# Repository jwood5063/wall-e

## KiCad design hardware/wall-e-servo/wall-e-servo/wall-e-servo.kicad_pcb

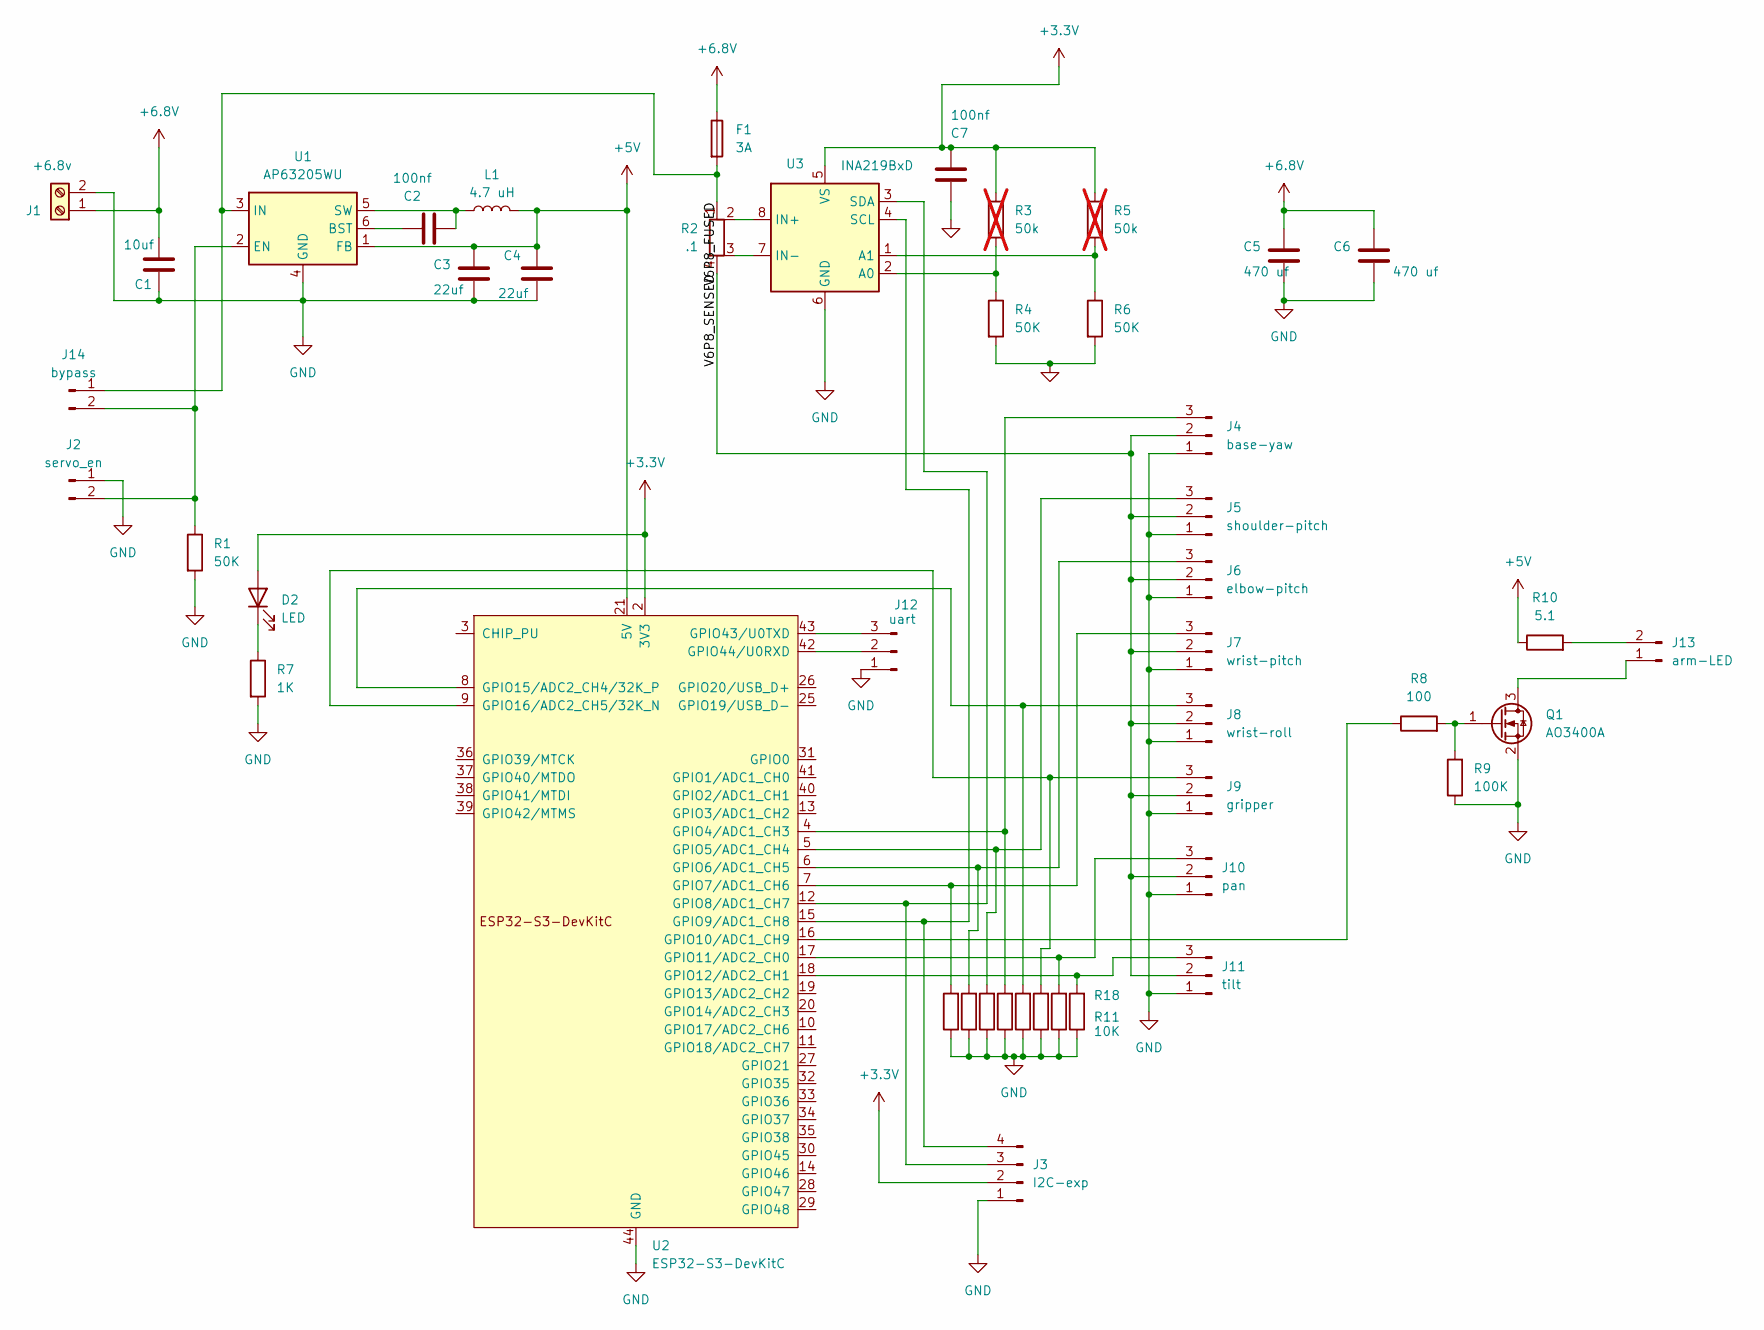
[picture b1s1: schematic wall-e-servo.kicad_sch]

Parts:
C1: 10uf; C_1210_3225Metric_Pad1.33x2.70mm_HandSolder
C2, C7: 100nf; C_0805_2012Metric_Pad1.18x1.45mm_HandSolder
C3, C4: 22uf; C_1210_3225Metric_Pad1.33x2.70mm_HandSolder
C5, C6: 470 uf; CP_Radial_D8.0mm_P3.50mm
D2: LED; LED_D5.0mm
F1: 3A; FuseHolder_Blade_ATO_Littelfuse_FLR_178.6165
J1: +6.8v; TerminalBlock_Phoenix_MKDS-1,5-2-5.08_1x02_P5.08mm_Horizont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
J2: servo_en; JST_PH_B2B-PH-K_1x02_P2.00mm_Vertical
J3: I2C-exp; JST_PH_B4B-PH-K_1x04_P2.00mm_Vertical
J4: base-yaw; PinHeader_1x03_P2.54mm_Vertical
J5: shoulder-pitch; PinHeader_1x03_P2.54mm_Vertical
J6: elbow-pitch; PinHeader_1x03_P2.54mm_Vertical
J7: wrist-pitch; PinHeader_1x03_P2.54mm_Vertical
J8: wrist-roll; PinHeader_1x03_P2.54mm_Vertical
J9: gripper; PinHeader_1x03_P2.54mm_Vertical
J10: pan; PinHeader_1x03_P2.54mm_Vertical
J11: tilt; PinHeader_1x03_P2.54mm_Vertical
J12: uart; JST_PH_B3B-PH-K_1x03_P2.00mm_Vertical
J13: arm-LED; JST_PH_B2B-PH-K_1x02_P2.00mm_Vertical
J14: bypass; PinHeader_1x02_P2.54mm_Vertical
L1: 4.7 uH; L_1806_4516Metric_Pad1.45x1.90mm_HandSolder
Q1: AO3400A; SOT-23
R1, R4, R6: 50K; R_0805_2012Metric_Pad1.20x1.40mm_HandSolder
R2: .1; R_Shunt_Vishay_WSK2512_6332Metric_T1.19mm
R3, R5: 50k; R_0805_2012Metric_Pad1.20x1.40mm_HandSolder; not fitted
R7: 1K; R_Axial_DIN0207_L6.3mm_D2.5mm_P10.16mm_Horizontal
R8: 100; R_0805_2012Metric_Pad1.20x1.40mm_HandSolder
R9: 100K; R_0805_2012Metric_Pad1.20x1.40mm_HandSolder
R10: 5.1; R_2512_6332Metric_Pad1.40x3.35mm_HandSolder
R11, R12, R13, R14, R15, R16, R17, R18: 10K; R_0805_2012Metric_Pad1.20x1.40mm_HandSolder
U1: AP63205WU; TSOT-23-6
U2: ESP32-S3-DevKitC
U3: INA219BxD; SOIC-8_3.9x4.9mm_P1.27mm

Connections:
+3.3V: C7.2, D2.2 (A), J3.2, R3.1, R5.1, U2.1 (3V3), U2.2 (3V3), U3.5 (VS)
+5V: C3.1, C4.1, L1.2, R10.1, U1.1 (FB), U2.21 (5V)
+6.8V: C1.1, C5.1, C6.1, F1.1, J1.1
/V6P8_FUSED: F1.2, J14.1, R2.1, U1.3 (IN)
/V6P8_SENSED: J4.2, J5.2, J6.2, J7.2, J8.2, J9.2, J10.2, J11.2, R2.4
GND: C1.2, C3.2, C4.2, C5.2, C6.2, C7.1, J1.2, J2.1, J3.1, J4.1, J5.1, J6.1, J7.1, J8.1, J9.1, J10.1, J11.1, J12.1, Q1.2 (S), R1.2, R4.2, R6.2, R7.2, R9.1, R11.1, R12.1, R13.1, R14.1, R15.1, R16.1, R17.1, R18.1, U1.4 (GND), U2.22 (GND), U2.23 (GND), U2.24 (GND), U2.44 (GND), U3.6 (GND)
unnamed: D2.1 (K), R7.1
unnamed: J3.3, U2.12 (GPIO8/ADC1_CH7), U3.3 (SDA)
unnamed: J3.4, U2.15 (GPIO9/ADC1_CH8), U3.4 (SCL)
unnamed: J4.3, R15.2, U2.4 (GPIO4/ADC1_CH3)
unnamed: J5.3, R16.2, U2.5 (GPIO5/ADC1_CH4)
unnamed: J6.3, R17.2, U2.6 (GPIO6/ADC1_CH5)
unnamed: J7.3, R18.2, U2.7 (GPIO7/ADC1_CH6)
unnamed: J8.3, R14.2, U2.8 (GPIO15/ADC2_CH4/32K_P)
unnamed: J9.3, R13.2, U2.9 (GPIO16/ADC2_CH5/32K_N)
unnamed: J10.3, R12.2, U2.17 (GPIO11/ADC2_CH0)
unnamed: J11.3, R11.2, U2.18 (GPIO12/ADC2_CH1)
unnamed: J12.2, U2.42 (GPIO44/U0RXD)
unnamed: J12.3, U2.43 (GPIO43/U0TXD)
unnamed: J13.1, Q1.3 (D)
unnamed: J13.2, R10.2
unnamed: J2.2, J14.2, R1.1, U1.2 (EN)
unnamed: Q1.1 (G), R8.2, R9.2
unnamed: C2.1, U1.6 (BST)
unnamed: C2.2, L1.1, U1.5 (SW)
unnamed: R8.1, U2.16 (GPIO10/ADC1_CH9)
unnamed: R3.2, R4.1, U3.2 (A0)
unnamed: R5.2, R6.1, U3.1 (A1)
unnamed: R2.2, U3.8 (IN+)
unnamed: R2.3, U3.7 (IN-)

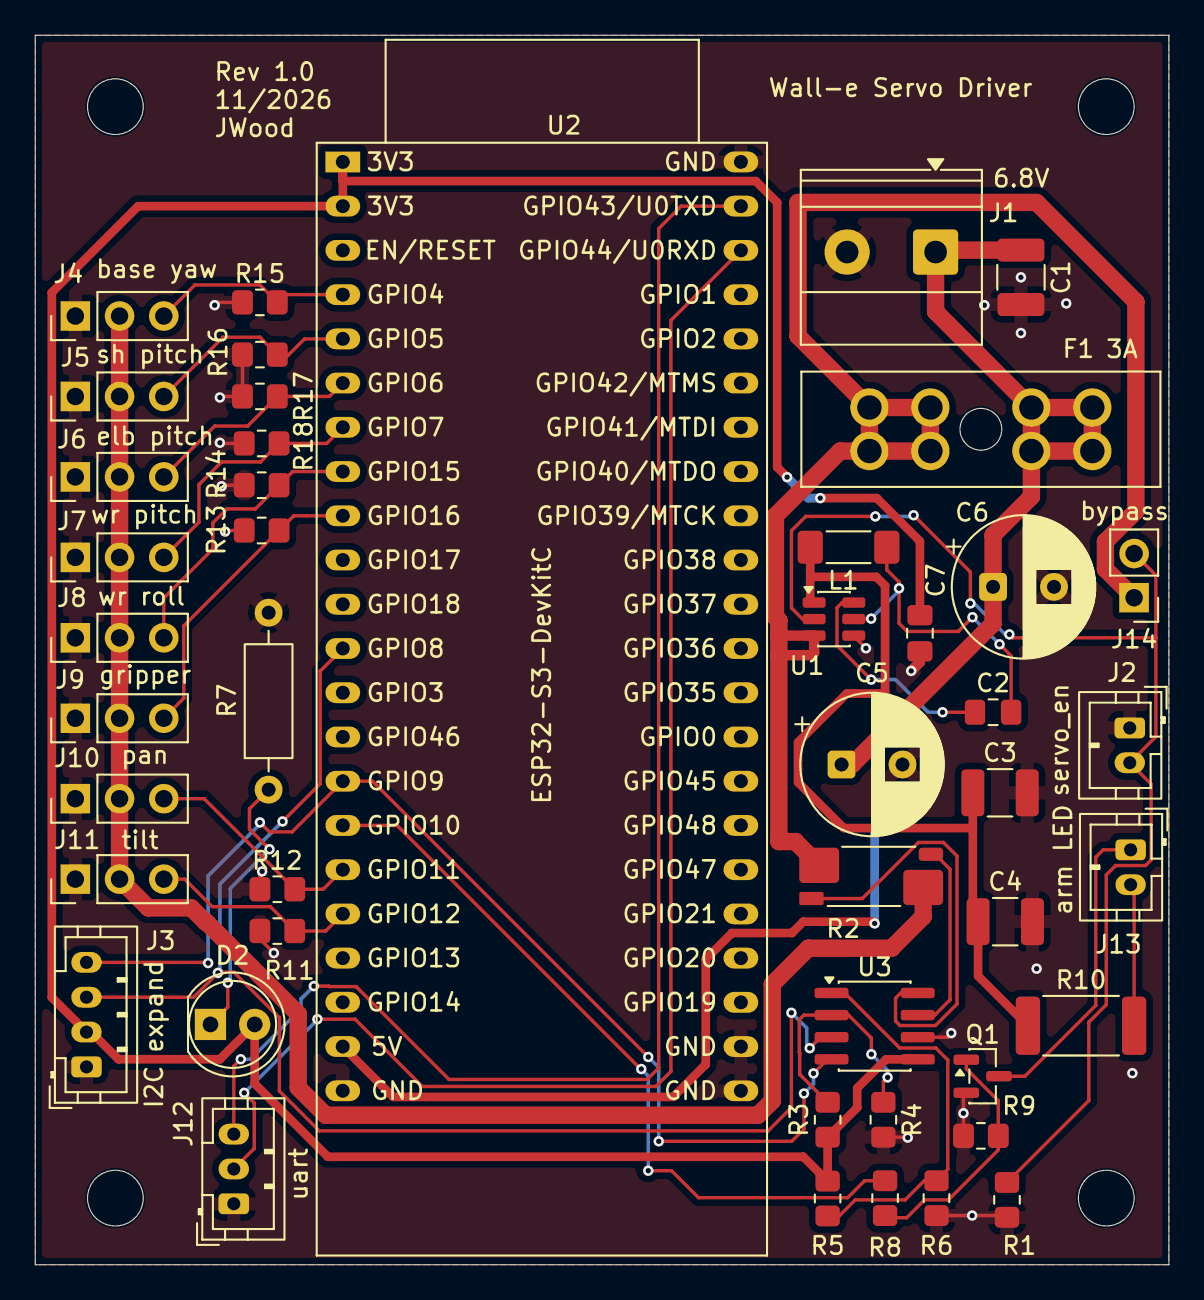
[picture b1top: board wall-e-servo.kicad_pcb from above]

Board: 2 copper layers, 65.1 x 70.6 mm, 46 parts (0 on the bottom side), 30 nets.

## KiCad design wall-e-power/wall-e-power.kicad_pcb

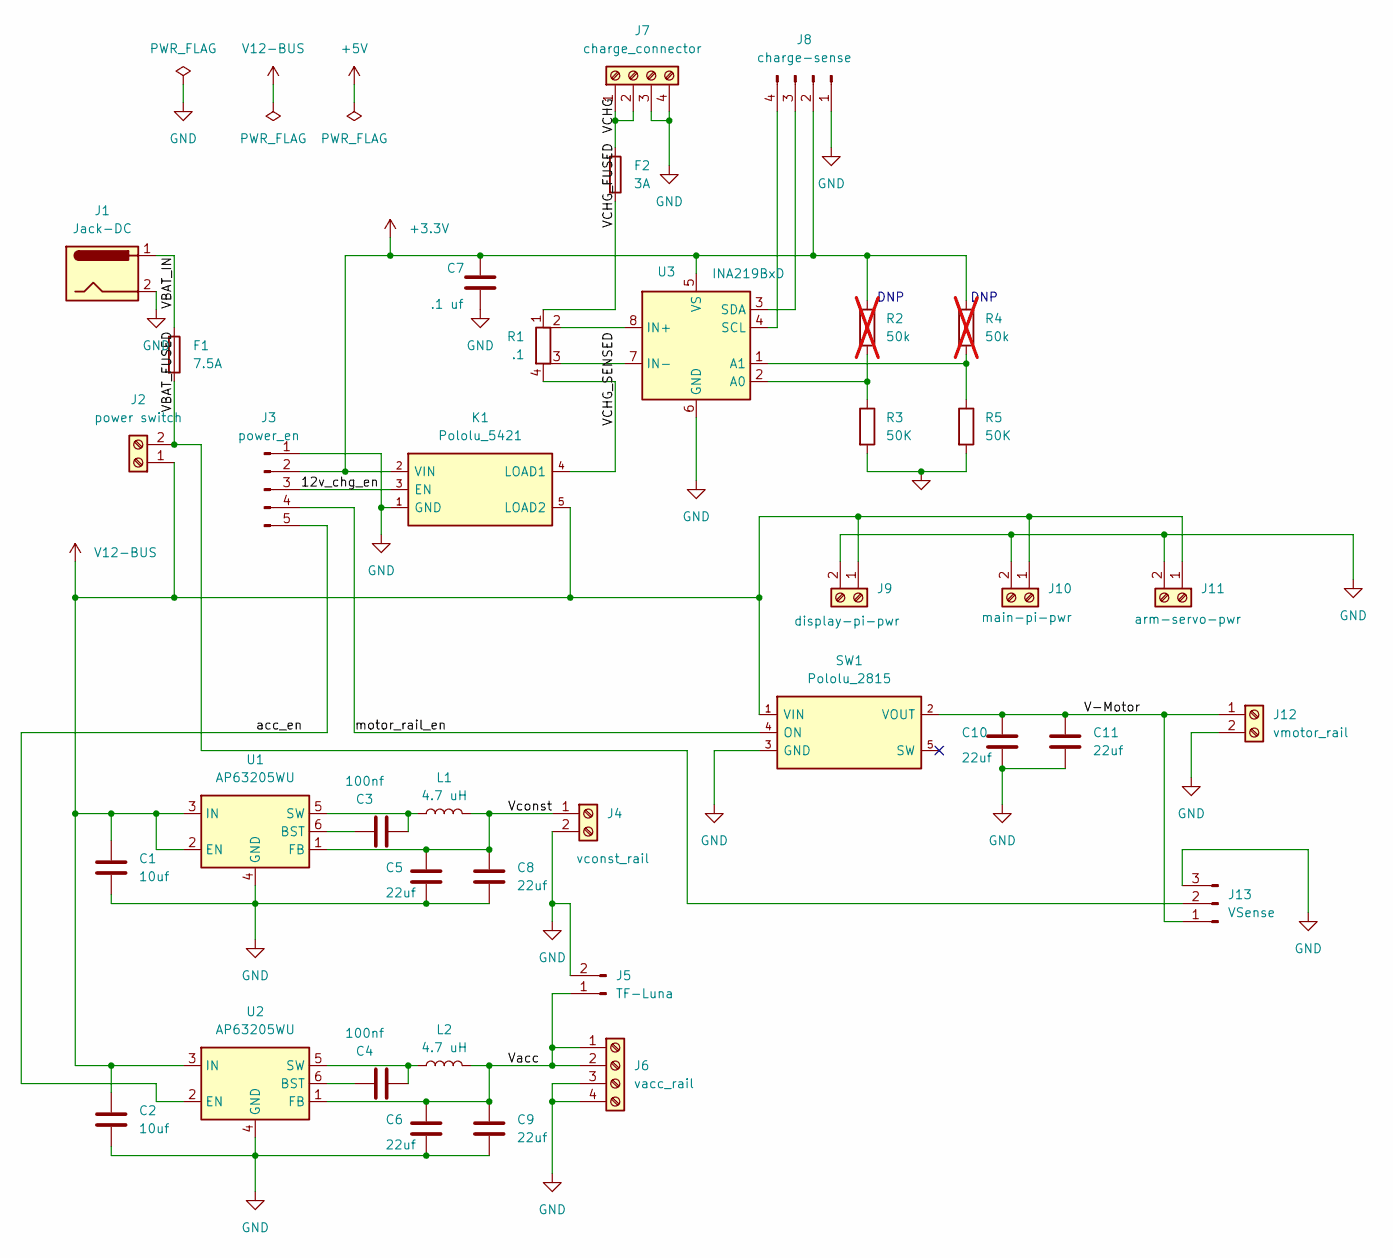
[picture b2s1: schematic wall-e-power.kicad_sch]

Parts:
C1, C2: 10uf; C_1210_3225Metric_Pad1.33x2.70mm_HandSolder
C3, C4: 100nf; C_0805_2012Metric_Pad1.18x1.45mm_HandSolder
C5, C6, C8, C9, C10, C11: 22uf; C_1210_3225Metric_Pad1.33x2.70mm_HandSolder
C7: .1 uf; C_0805_2012Metric_Pad1.18x1.45mm_HandSolder
F1: 7.5A; FuseHolder_Blade_ATO_Littelfuse_FLR_178.6165
F2: 3A; FuseHolder_Blade_ATO_Littelfuse_FLR_178.6165
J1: Jack-DC; BarrelJack_Tensility_54-00131
J2: power switch; TerminalBlock_Phoenix_MKDS-1,5-2-5.08_1x02_P5.08mm_Horizont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
J3: power_en; JST_PH_B5B-PH-K_1x05_P2.00mm_Vertical
J4: vconst_rail; TerminalBlock_Phoenix_MKDS-1,5-2-5.08_1x02_P5.08mm_Horizont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
J5: TF-Luna; JST_PH_B2B-PH-K_1x02_P2.00mm_Vertical
J6: vacc_rail; TerminalBlock_RND_205-00003_1x04_P5.00mm_Horizontal
J7: charge_connector; TerminalBlock_RND_205-00003_1x04_P5.00mm_Horizontal
J8: charge-sense; JST_PH_B4B-PH-K_1x04_P2.00mm_Vertical
J9: display-pi-pwr; TerminalBlock_Phoenix_MKDS-1,5-2-5.08_1x02_P5.08mm_Horizont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
J10: main-pi-pwr; TerminalBlock_Phoenix_MKDS-1,5-2-5.08_1x02_P5.08mm_Horizont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
J11: arm-servo-pwr; TerminalBlock_Phoenix_MKDS-1,5-2-5.08_1x02_P5.08mm_Horizont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
J12: vmotor_rail; TerminalBlock_Phoenix_MKDS-1,5-2-5.08_1x02_P5.08mm_Horizont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
J13: VSense; JST_PH_B3B-PH-K_1x03_P2.00mm_Vertical
K1: Pololu_5421; Pololu_5421_THT
L1, L2: 4.7 uH; L_1806_4516Metric_Pad1.45x1.90mm_HandSolder
R1: .1; R_Shunt_Vishay_WSK2512_6332Metric_T1.19mm
R2, R4: 50k; R_0805_2012Metric_Pad1.20x1.40mm_HandSolder; not fitted
R3, R5: 50K; R_0805_2012Metric_Pad1.20x1.40mm_HandSolder
SW1: Pololu_2815; Pololu_2815_THT
U1, U2: AP63205WU; TSOT-23-6
U3: INA219BxD; SOIC-8_3.9x4.9mm_P1.27mm

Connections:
+3.3V: C7.1, J3.2, J8.2, K1.2 (VIN), R2.1, R4.1, U3.5 (VS)
/12v_chg_en: J3.3, K1.3 (EN)
/V-Motor: C10.1, C11.1, J12.1, J13.1, SW1.2 (VOUT)
/VBAT_FUSED: F1.2, J2.2, J13.2
/VBAT_IN: F1.1, J1.1
/VCHG: F2.1, J7.1, J7.2
/VCHG_FUSED: F2.2, R1.1
/VCHG_SENSED: K1.4 (LOAD1), R1.4
/Vacc: C6.1, C9.1, J5.1, J6.1, J6.2, L2.2, U2.1 (FB)
/Vconst: C5.1, C8.1, J4.1, L1.2, U1.1 (FB)
/acc_en: J3.5, U2.2 (EN)
/motor_rail_en: J3.4, SW1.4 (ON)
GND: C1.2, C2.2, C5.2, C6.2, C7.2, C8.2, C9.2, C10.2, C11.2, J1.2, J3.1, J4.2, J5.2, J6.3, J6.4, J7.3, J7.4, J8.1, J9.2, J10.2, J11.2, J12.2, J13.3, K1.1 (GND), R3.2, R5.2, SW1.3 (GND), U1.4 (GND), U2.4 (GND), U3.6 (GND)
unnamed: J8.3, U3.3 (SDA)
unnamed: J8.4, U3.4 (SCL)
unnamed: C3.1, U1.6 (BST)
unnamed: C3.2, L1.1, U1.5 (SW)
unnamed: C4.1, U2.6 (BST)
unnamed: C4.2, L2.1, U2.5 (SW)
unnamed: R2.2, R3.1, U3.2 (A0)
unnamed: R4.2, R5.1, U3.1 (A1)
unnamed: R1.2, U3.8 (IN+)
unnamed: R1.3, U3.7 (IN-)
V12-BUS: C1.1, C2.1, J2.1, J9.1, J10.1, J11.1, K1.5 (LOAD2), SW1.1 (VIN), U1.2 (EN), U1.3 (IN), U2.3 (IN)

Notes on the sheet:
DNP
DNP

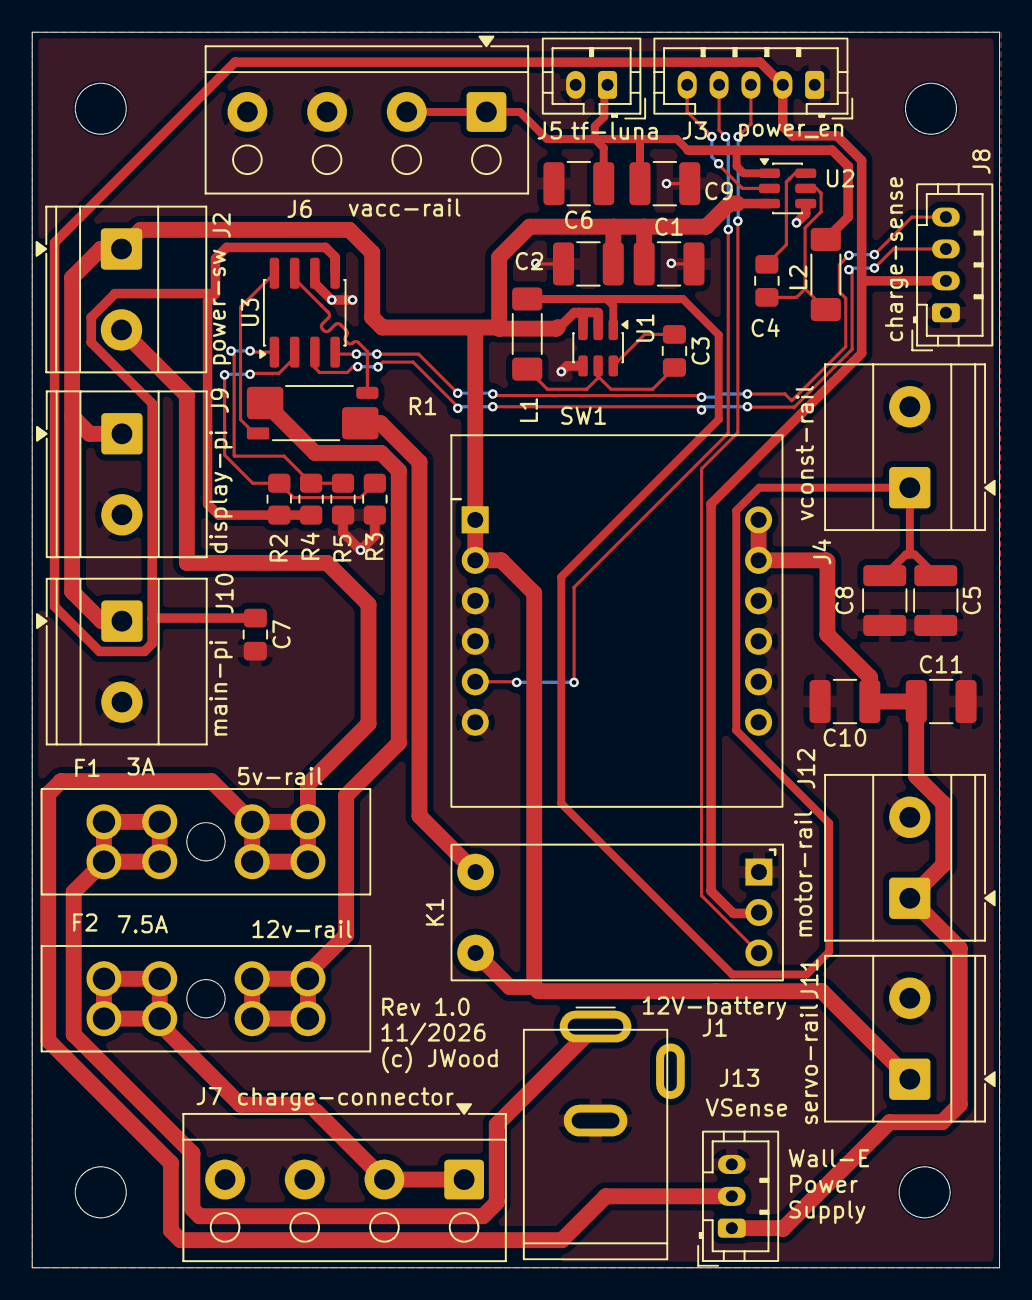
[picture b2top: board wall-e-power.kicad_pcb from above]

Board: 2 copper layers, 60.7 x 77.5 mm, 38 parts (0 on the bottom side), 24 nets.

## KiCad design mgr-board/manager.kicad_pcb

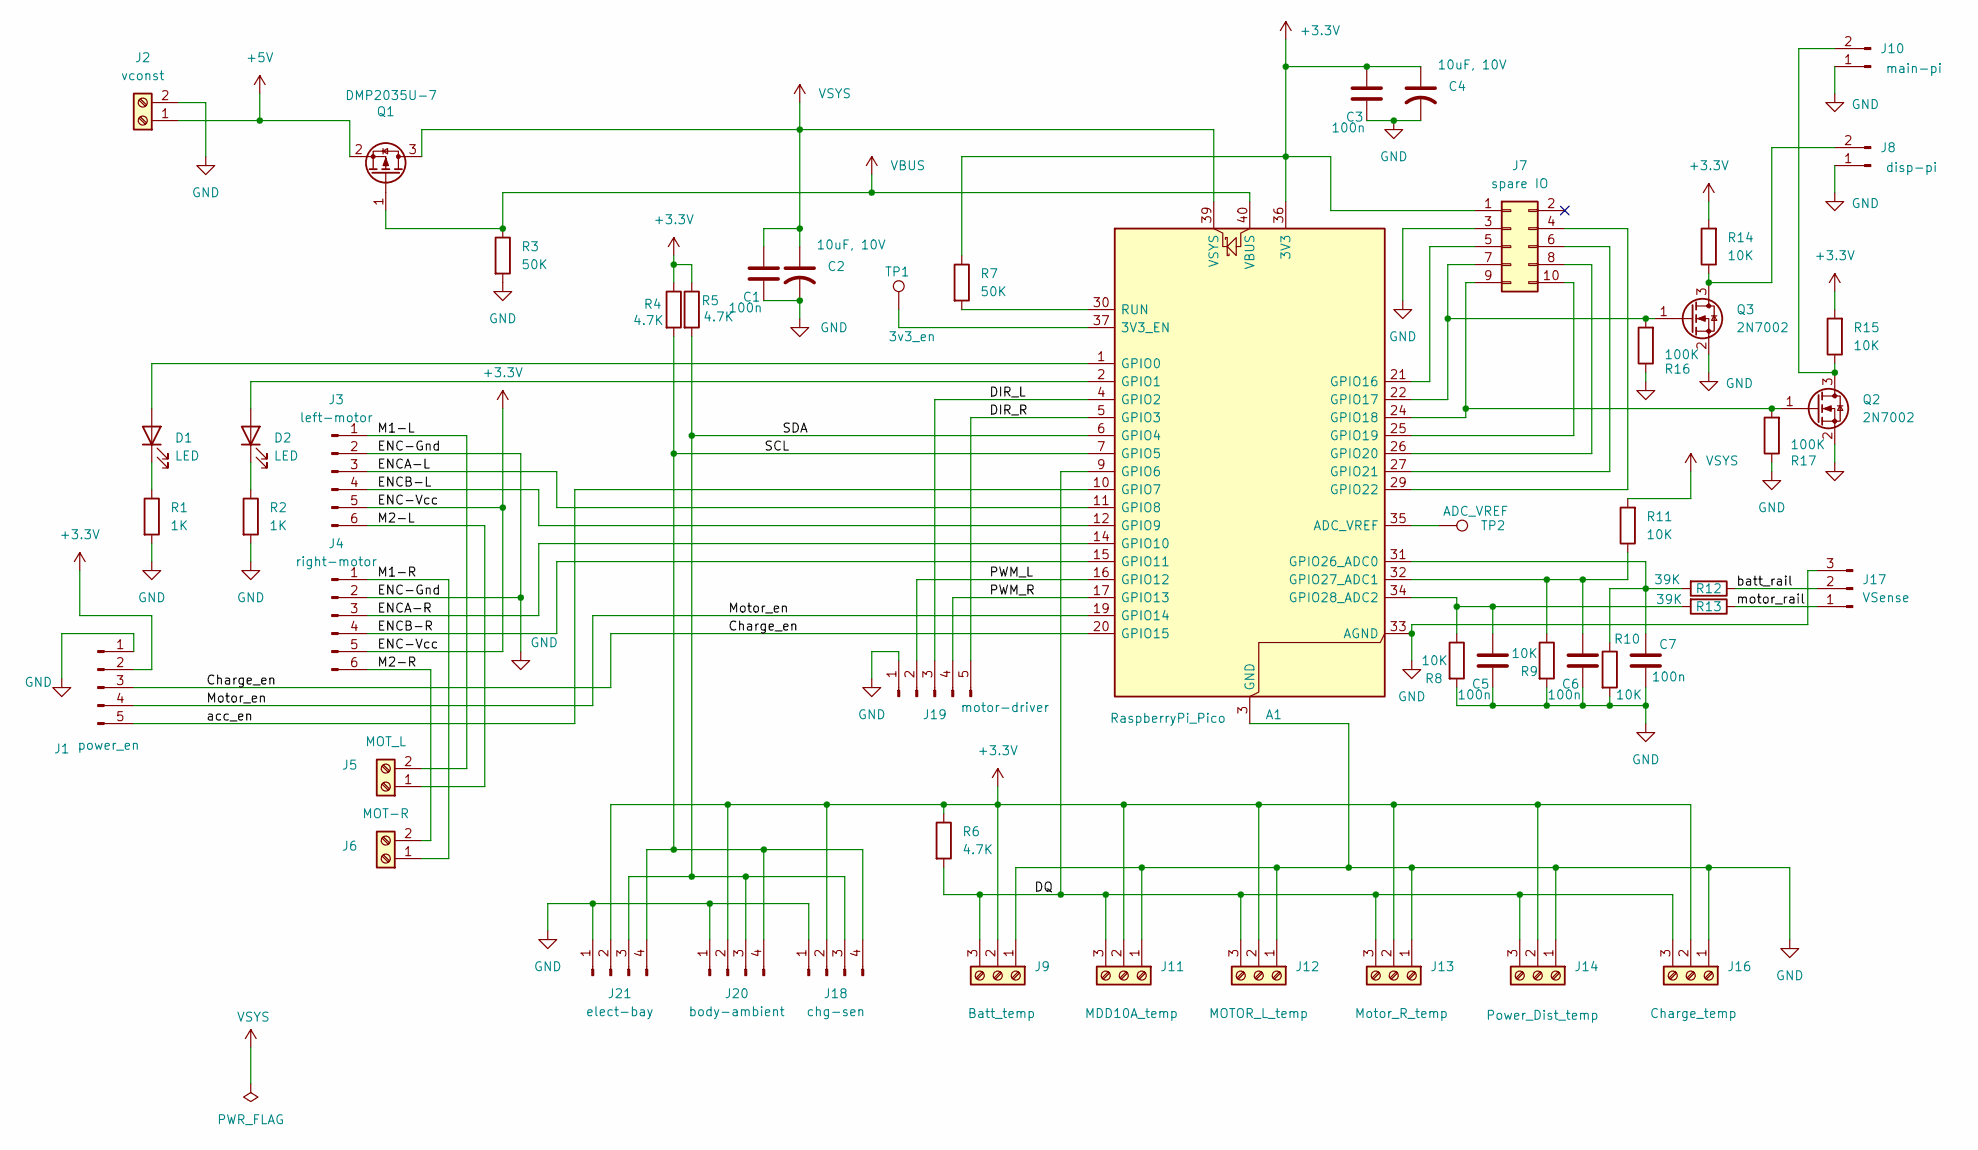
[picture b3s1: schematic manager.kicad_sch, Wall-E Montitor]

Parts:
A1: RaspberryPi_Pico; RaspberryPi_Pico_Common_THT
C1, C3, C5, C6, C7: 100n; C_Disc_D5.0mm_W2.5mm_P2.50mm
C2, C4: 10uF, 10V; C_Radial_D4.0mm_H5.0mm_P1.50mm
D1, D2: LED; LED_D5.0mm
J1: power_en; JST_PH_B5B-PH-K_1x05_P2.00mm_Vertical
J2: vconst; TerminalBlock_RND_205-00012_1x02_P5.00mm_Horizontal
J3: left-motor; JST_PH_B6B-PH-K_1x06_P2.00mm_Vertical
J4: right-motor; JST_PH_B6B-PH-K_1x06_P2.00mm_Vertical
J5: MOT_L; TerminalBlock_RND_205-00012_1x02_P5.00mm_Horizontal
J6: MOT-R; TerminalBlock_RND_205-00012_1x02_P5.00mm_Horizontal
J7: spare IO; PinHeader_2x05_P2.54mm_Vertical
J8: disp-pi; JST_PH_B2B-PH-K_1x02_P2.00mm_Vertical
J9: Batt_temp; TerminalBlock_RND_205-00002_1x03_P5.00mm_Horizontal
J10: main-pi; JST_PH_B2B-PH-K_1x02_P2.00mm_Vertical
J11: MDD10A_temp; TerminalBlock_RND_205-00002_1x03_P5.00mm_Horizontal
J12: MOTOR_L_temp; TerminalBlock_RND_205-00002_1x03_P5.00mm_Horizontal
J13: Motor_R_temp; TerminalBlock_RND_205-00002_1x03_P5.00mm_Horizontal
J14: Power_Dist_temp; TerminalBlock_RND_205-00002_1x03_P5.00mm_Horizontal
J16: Charge_temp; TerminalBlock_RND_205-00002_1x03_P5.00mm_Horizontal
J17: VSense; JST_PH_B3B-PH-K_1x03_P2.00mm_Vertical
J18: chg-sen; JST_PH_B4B-PH-K_1x04_P2.00mm_Vertical
J19: motor-driver; JST_PH_B5B-PH-K_1x05_P2.00mm_Vertical
J20: body-ambient; JST_PH_B4B-PH-K_1x04_P2.00mm_Vertical
J21: elect-bay; JST_PH_B4B-PH-K_1x04_P2.00mm_Vertical
Q1: DMP2035U-7; SOT-23
Q2, Q3: 2N7002; SOT-23
R1, R2: 1K; R_Axial_DIN0207_L6.3mm_D2.5mm_P10.16mm_Horizontal
R3, R7: 50K; R_Axial_DIN0207_L6.3mm_D2.5mm_P10.16mm_Horizontal
R4, R5, R6: 4.7K; R_Axial_DIN0207_L6.3mm_D2.5mm_P10.16mm_Horizontal
R8, R9, R10, R11, R14, R15: 10K; R_Axial_DIN0207_L6.3mm_D2.5mm_P10.16mm_Horizontal
R12, R13: 39K; R_Axial_DIN0207_L6.3mm_D2.5mm_P10.16mm_Horizontal
R16, R17: 100K; R_Axial_DIN0207_L6.3mm_D2.5mm_P10.16mm_Horizontal
TP1: 3v3_en; PinHeader_1x01_P2.54mm_Vertical
TP2: ADC_VREF; PinHeader_1x01_P2.54mm_Vertical

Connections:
+3.3V: A1.36 (3V3), C3.1, C4.1, J1.2, J3.5, J4.5, J7.1, J9.2, J11.2, J12.2, J13.2, J14.2, J16.2, J18.2, J20.2, J21.2, R4.1, R5.1, R6.1, R7.1, R14.2, R15.2
+5V: J2.1, Q1.2 (S)
/Charge_en: A1.20 (GPIO15), J1.3
/DIR_L: A1.4 (GPIO2), J19.3
/DIR_R: A1.5 (GPIO3), J19.5
/DQ: A1.9 (GPIO6), J9.3, J11.3, J12.3, J13.3, J14.3, J16.3, R6.2
/ENCA-L: A1.11 (GPIO8), J3.3
/ENCA-R: A1.14 (GPIO10), J4.3
/ENCB-L: A1.12 (GPIO9), J3.4
/ENCB-R: A1.15 (GPIO11), J4.4
/M1-L: J3.1, J5.2
/M1-R: J4.1, J6.1
/M2-L: J3.6, J5.1
/M2-R: J4.6, J6.2
/Motor_en: A1.19 (GPIO14), J1.4
/PWM_L: A1.16 (GPIO12), J19.2
/PWM_R: A1.17 (GPIO13), J19.4
/SCL: A1.7 (GPIO5), J18.4, J20.4, J21.4, R4.2
/SDA: A1.6 (GPIO4), J18.3, J20.3, J21.3, R5.2
/acc_en: A1.10 (GPIO7), J1.5
/batt_rail: J17.2, R12.1
/motor_rail: J17.1, R13.1
GND: A1.3 (GND), A1.8 (GND), A1.13 (GND), A1.18 (GND), A1.23 (GND), A1.28 (GND), A1.33 (AGND), A1.38 (GND), C1.2, C2.2, C3.2, C4.2, C5.2, C6.2, C7.2, J1.1, J2.2, J3.2, J4.2, J7.3, J8.1, J9.1, J10.1, J11.1, J12.1, J13.1, J14.1, J16.1, J17.3, J18.1, J19.1, J20.1, J21.1, Q2.2 (S), Q3.2 (S), R1.2, R2.2, R3.2, R8.2, R9.2, R10.2, R16.1, R17.1; also elsewhere on the board
unnamed: A1.37 (3V3_EN), TP1.1 (1_1)
unnamed: A1.35 (ADC_VREF), TP2.1 (1_1)
unnamed: A1.1 (GPIO0), D1.2 (A)
unnamed: A1.2 (GPIO1), D2.2 (A)
unnamed: A1.21 (GPIO16), J7.5
unnamed: A1.22 (GPIO17), J7.7, Q3.1 (G), R16.2
unnamed: A1.24 (GPIO18), J7.9, Q2.1 (G), R17.2
unnamed: A1.25 (GPIO19), J7.10
unnamed: A1.26 (GPIO20), J7.8
unnamed: A1.27 (GPIO21), J7.6
unnamed 33: A1.29 (GPIO22), J7.4; also elsewhere on the board
unnamed: A1.31 (GPIO26_ADC0), C7.1, R10.1, R12.2
unnamed: A1.32 (GPIO27_ADC1), C6.1, R9.1, R11.1
unnamed: A1.34 (GPIO28_ADC2), C5.1, R8.1, R13.2
unnamed: A1.30 (RUN), R7.2
unnamed: D1.1 (K), R1.1
unnamed: D2.1 (K), R2.1
unnamed: J8.2, Q3.3 (D), R14.1
unnamed: J10.2, Q2.3 (D), R15.1
VBUS: A1.40 (VBUS), Q1.1 (G), R3.1
VSYS: A1.39 (VSYS), C1.1, C2.1, Q1.3 (D), R11.2

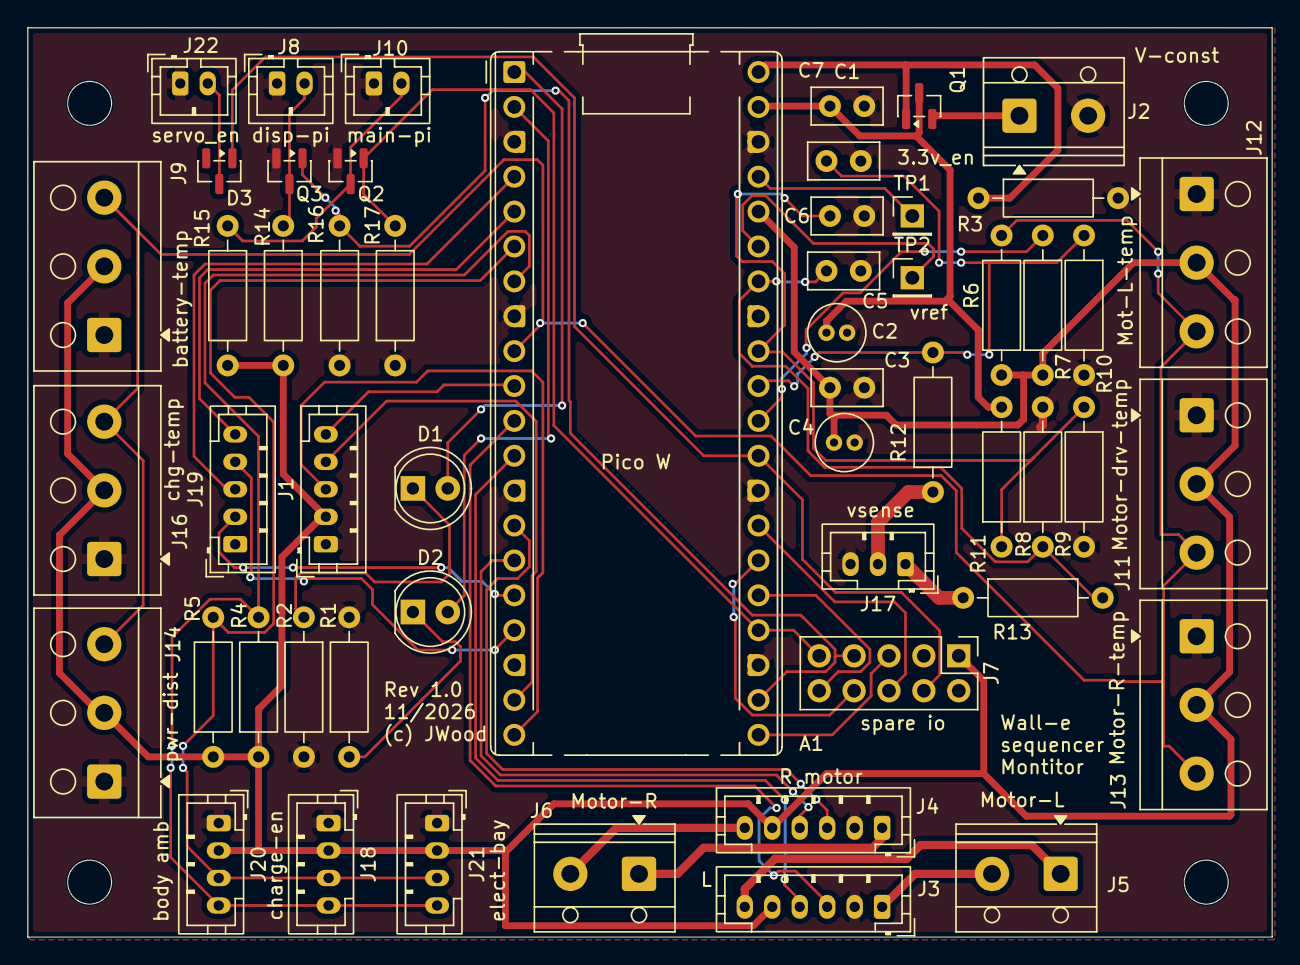
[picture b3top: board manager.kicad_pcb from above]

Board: 2 copper layers, 90.6 x 66.2 mm, 54 parts (0 on the bottom side), 45 nets.

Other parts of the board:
D3: BAT54C; SOT-23
J22: servo_en; JST_PH_B2B-PH-K_1x02_P2.00mm_Vertical

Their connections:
GND: J22.1; also elsewhere on the board
unnamed 33: D3.1; also elsewhere on the board
unnamed: D3.3, J22.2

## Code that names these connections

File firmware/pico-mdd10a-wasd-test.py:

# pico-mdd10a-wasd-test.py
# MicroPython bench test for the Cytron MDD10A, driven by the Pico over USB serial.
#
# Keys (in the serial terminal / REPL):
#   w = both motors forward      s = both motors reverse
#   a = pivot left  (L rev, R fwd)   d = pivot right (L fwd, R rev)
#   x or SPACE = stop
#   + / - = speed up / slow down (10% steps, applies to the next command)
#   h = help
#
# Wiring (Pico carrier J2 assignment, verified 2026-11-05):
#   PWM_L = GP12, DIR_L = GP2, PWM_R = GP13, DIR_R = GP3, common GND.
# Sign-magnitude drive per the MDD10A truth table: DIR low = forward
# (output A high), DIR high = reverse; speed = PWM duty. PWM at 20 kHz,
# the MDD10A's rated maximum. Duty ramps so the motors (or the meter, in
# the unloaded test) never see a step change.
#
# Note: with a straight cable to the MDD10A today, these "left" signals land
# on the driver's channel 2 and "right" on channel 1 (the board's input order
# is PWM2/DIR2 before PWM1/DIR1). Irrelevant for this test; the carrier J2
# re-pin to match is a recorded relayout to-do (2026-11-16).

import sys
import select
import time
from machine import Pin, PWM

PWM_FREQ = 20000
RAMP_STEP = 0.05          # duty change per tick (~0.4 s from stop to full)
TICK_MS = 20

pwm_l = PWM(Pin(12))
pwm_l.freq(PWM_FREQ)
dir_l = Pin(2, Pin.OUT, value=0)
pwm_r = PWM(Pin(13))
pwm_r.freq(PWM_FREQ)
dir_r = Pin(3, Pin.OUT, value=0)


def drive(pwm, dir_pin, value):
    """value: -1.0..1.0, sign = direction, magnitude = duty."""
    dir_pin.value(0 if value >= 0 else 1)
    pwm.duty_u16(int(abs(value) * 65535))


def stop_all():
    drive(pwm_l, dir_l, 0)
    drive(pwm_r, dir_r, 0)


speed = 0.4               # commanded duty for w/a/s/d, adjustable with +/-
cur_l = cur_r = 0.0       # ramped (actual) outputs
tgt_l = tgt_r = 0.0       # commanded targets

COMMANDS = {
    "w": lambda s: (s, s),
    "s": lambda s: (-s, -s),
    "a": lambda s: (-s, s),   # pivot left: left track back, right track forward
    "d": lambda s: (s, -s),   # pivot right
}

HELP = __doc__

print("MDD10A WASD test — PWM_L GP12, DIR_L GP2, PWM_R GP13, DIR_R GP3")
print("w/a/s/d drive, x or space stops, +/- speed, h help. Speed starts at 40%.")

poller = select.poll()
poller.register(sys.stdin, select.POLLIN)
stdin = sys.stdin.buffer if hasattr(sys.stdin, "buffer") else sys.stdin

try:
    while True:
        if poller.poll(0):
            ch = stdin.read(1).decode().lower()
            if ch in COMMANDS:
                tgt_l, tgt_r = COMMANDS[ch](speed)
                print("cmd", ch, "-> L {:+.0f}%  R {:+.0f}%".format(tgt_l * 100, tgt_r * 100))
            elif ch in ("x", " "):
                tgt_l = tgt_r = 0.0
                print("stop")
            elif ch in ("+", "="):
                speed = min(1.0, speed + 0.1)
                print("speed {:.0f}% (applies to next w/a/s/d)".format(speed * 100))
            elif ch == "-":
                speed = max(0.1, speed - 0.1)
                print("speed {:.0f}% (applies to next w/a/s/d)".format(speed * 100))
            elif ch == "h":
                print(HELP)
            # anything else (incl. \r, \n) is ignored

        # Ramp actual outputs toward targets, then apply.
        for name in ("l", "r"):
            cur = cur_l if name == "l" else cur_r
            tgt = tgt_l if name == "l" else tgt_r
            if cur < tgt:
                cur = min(tgt, cur + RAMP_STEP)
            elif cur > tgt:
                cur = max(tgt, cur - RAMP_STEP)
            if name == "l":
                cur_l = cur
            else:
                cur_r = cur
        drive(pwm_l, dir_l, cur_l)
        drive(pwm_r, dir_r, cur_r)

        time.sleep_ms(TICK_MS)
except KeyboardInterrupt:
    pass
finally:
    stop_all()
    pwm_l.deinit()
    pwm_r.deinit()
    print("stopped, PWM off")
